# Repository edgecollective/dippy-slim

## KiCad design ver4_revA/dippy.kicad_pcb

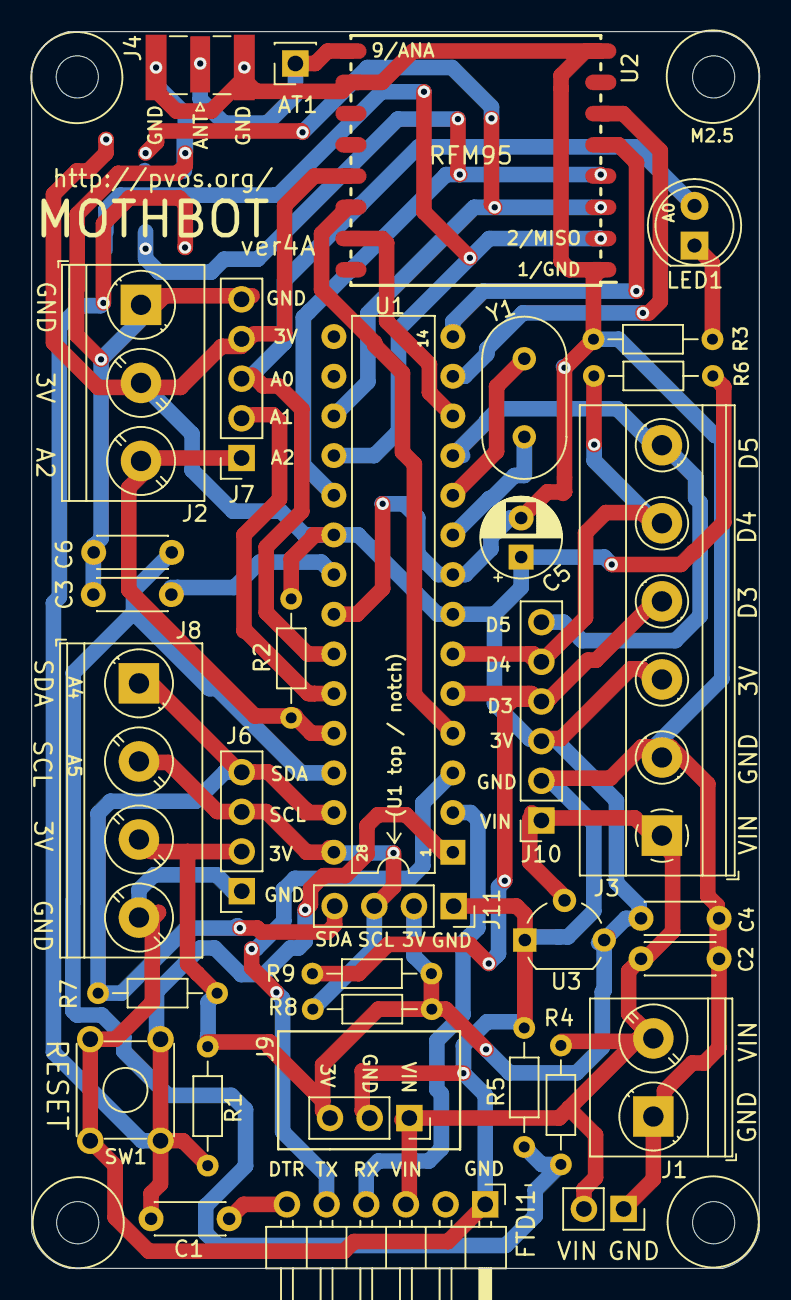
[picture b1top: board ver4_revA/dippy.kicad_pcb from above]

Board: 2 copper layers, 46.6 x 79.2 mm, 39 parts (1 on the bottom side), 28 nets.

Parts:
AT1: Conn_01x01_Female; PinSocket_1x01_P2.54mm_Vertical
C1, C2, C3, C4: 0.1u; C_Disc_D4.3mm_W1.9mm_P5.00mm
C5: 10u; CP_Radial_D5.0mm_P2.50mm
C6: 0.1uF; C_Disc_D4.3mm_W1.9mm_P5.00mm
FTDI1: Conn_01x06_Male; PinHeader_1x06_P2.54mm_Horizontal
H1, H2, H3, H4: MountingHole; MountingHole_2.7mm_M2.5
J1: Screw_Terminal_01x02; TerminalBlock_Phoenix_PT-1,5-2-5.0-H_1x02_P5.00mm_Horizontal
J2: Screw_Terminal_01x03; TerminalBlock_Phoenix_PT-1,5-3-5.0-H_1x03_P5.00mm_Horizontal
J3: Screw_Terminal_01x06; TerminalBlock_Phoenix_MKDS-1,5-6_1x06_P5.00mm_Horizontal
J4: Conn_Coaxial; SMA_Samtec_SMA-J-P-X-ST-EM1_EdgeMount
J5: Conn_02x03_Odd_Even; PinSocket_2x03_P2.54mm_Vertical_SMD
J6, J11: Conn_01x04_Female; PinSocket_1x04_P2.54mm_Vertical
J7: Conn_01x05_Female; PinSocket_1x05_P2.54mm_Vertical
J8: Screw_Terminal_01x04; TerminalBlock_Phoenix_PT-1,5-4-5.0-H_1x04_P5.00mm_Horizontal
J9: Conn_01x03_Female; PinSocket_1x03_P2.54mm_Vertical
J10: Conn_01x06_Female; PinSocket_1x06_P2.54mm_Vertical
J12: Conn_01x02_Female; PinSocket_1x02_P2.54mm_Vertical
LED1: LED; LED_D5.0mm
R1, R2, R3, R9: 10K; R_Axial_DIN0204_L3.6mm_D1.6mm_P7.62mm_Horizontal
R4, R5: 10M; R_Axial_DIN0204_L3.6mm_D1.6mm_P7.62mm_Horizontal
R6: 300R; R_Axial_DIN0204_L3.6mm_D1.6mm_P7.62mm_Horizontal
R7, R8: R; R_Axial_DIN0204_L3.6mm_D1.6mm_P7.62mm_Horizontal
SW1: SW_Push_Dual; SW_TH_Tactile_Omron_B3F-10xx
U1: ATmega328P-PU-C; DIP-28_W7.62mm
U2: RFM95W-915S2; RFM95
U3: MCP1700-3302E_TO92; TO-92_Wide
Y1: Crystal; Resonator-2Pin_W10.0mm_H5.0mm

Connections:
A0: J7.3, LED1.2, U1.23
A1: J7.2, U1.24
A2: J2.3, J7.1, R2.2, U1.25
A3: C6.1, R4.2, R5.1, U1.26
A4: J6.4, J8.1, J11.4, R7.2, U1.27
A5: J6.3, J8.2, J11.3, R8.2, U1.28
D2: U1.4, U2.14
D3: J3.4, J10.4, R9.2, U1.5
D4: J3.5, J10.5, R3.2, U1.6
D5: J3.6, J10.6, U1.11
D6: U1.12, U2.15
D7: U1.13, U2.6
D8: U1.14, U2.5
GND: C2.2, C3.2, C4.2, C5.2, C6.2, FTDI1.1, J1.1, J2.1, J3.2, J4.2, J5.6, J6.1, J7.5, J8.4, J9.2, J10.2, J11.1, J12.1, R5.2, R6.2, SW1.3, SW1.4, U1.8, U1.22, U2.1, U2.8, U2.10, U3.1
MISO: J5.1, U1.18, U2.2
MOSI: J5.4, U1.17, U2.3
unnamed: AT1.1, J4.1, U2.9
unnamed: C1.2, FTDI1.6
unnamed: C3.1, U1.21
unnamed: LED1.1, R6.1
unnamed: U1.9, Y1.1
unnamed: U1.10, Y1.2
RST: C1.1, J5.5, R1.2, SW1.1, SW1.2, U1.1
RX0: FTDI1.4, U1.2
SCK: J5.3, U1.19, U2.4
TX0: FTDI1.5, U1.3
VCC: C4.1, C5.1, J2.2, J3.3, J5.2, J6.2, J7.4, J8.3, J9.3, J10.3, J11.2, R1.1, R2.1, R3.1, R7.1, R8.1, R9.1, U1.7, U1.20, U2.13, U3.3
VIN: C2.1, FTDI1.3, J1.2, J3.1, J9.1, J10.1, J12.2, R4.1, U3.2

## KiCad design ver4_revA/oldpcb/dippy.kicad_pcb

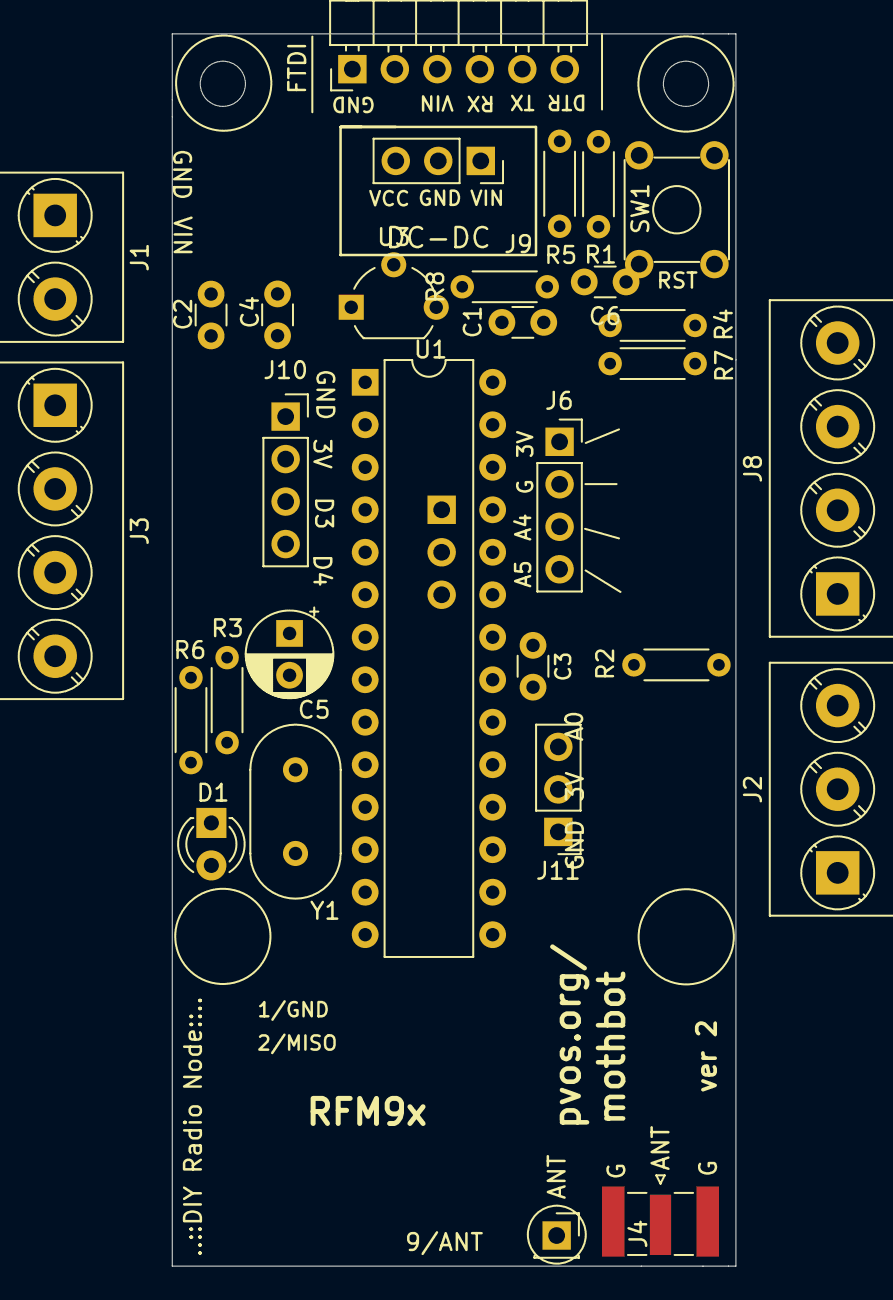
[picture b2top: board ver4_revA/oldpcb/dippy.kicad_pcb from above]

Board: 2 copper layers, 33.7 x 73.7 mm, 35 parts (1 on the bottom side), 21 nets, no tracks yet.

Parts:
AT1: Conn_01x01_Female; PinSocket_1x01_P2.54mm_Vertical
C1, C2, C3, C4: 0.1u; C_Disc_D3.0mm_W1.6mm_P2.50mm
C5: 10u; CP_Radial_D5.0mm_P2.50mm
C6: 0.1uF; C_Disc_D3.0mm_W1.6mm_P2.50mm
D1: LED; LED_D3.0mm
FTDI1: Conn_01x06_Male; PinHeader_1x06_P2.54mm_Horizontal
H1, H2, H3, H4: MountingHole; MountingHole_2.7mm_M2.5
J1: Screw_Terminal_01x02; TerminalBlock_Phoenix_PT-1,5-2-5.0-H_1x02_P5.00mm_Horizontal
J2: Screw_Terminal_01x03; TerminalBlock_Phoenix_PT-1,5-3-5.0-H_1x03_P5.00mm_Horizontal
J3, J8: Screw_Terminal_01x04; TerminalBlock_Phoenix_PT-1,5-4-5.0-H_1x04_P5.00mm_Horizontal
J4: Conn_Coaxial; SMA_Samtec_SMA-J-P-X-ST-EM1_EdgeMount
J6, J10: Conn_01x04_Female; PinSocket_1x04_P2.54mm_Vertical
J7, J11: Conn_01x03_Female; PinHeader_1x03_P2.54mm_Vertical
J9: Conn_01x03_Female; PinSocket_1x03_P2.54mm_Vertical
R1, R2, R3: 10K; R_Axial_DIN0204_L3.6mm_D1.6mm_P5.08mm_Horizontal
R4, R5: 10M; R_Axial_DIN0204_L3.6mm_D1.6mm_P5.08mm_Horizontal
R6: 300R; R_Axial_DIN0204_L3.6mm_D1.6mm_P5.08mm_Horizontal
R7, R8: R; R_Axial_DIN0204_L3.6mm_D1.6mm_P5.08mm_Horizontal
SW1: SW_Push_Dual; SW_TH_Tactile_Omron_B3F-10xx
U1: ATmega328P-PU-C; DIP-28_W7.62mm
U3: MCP1700-3302E_TO92; TO-92_Wide
Y1: Crystal; Resonator-2Pin_W10.0mm_H5.0mm

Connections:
A0: J2.3, J11.3, R2.2, U1.23
A1: J7.2, U1.24
A2: J7.1, U1.25
A3: C6.1, R4.2, R5.1, U1.26
A4: J6.4, J8.1, R7.2, U1.27
A5: J6.3, J8.2, R8.2, U1.28
D3: J3.3, J10.3, U1.5
D4: J3.4, J10.4, R3.2, U1.6
D5: D1.2, U1.11
GND: C2.2, C3.2, C4.2, C5.2, C6.2, FTDI1.1, J1.1, J2.1, J3.1, J4.2, J6.2, J7.3, J8.3, J9.2, J10.1, J11.1, R5.2, R6.2, SW1.3, SW1.4, U1.8, U1.22, U3.1
unnamed: AT1.1, J4.1
unnamed: C1.2, FTDI1.6
unnamed: C3.1, U1.21
unnamed: D1.1, R6.1
unnamed: U1.9, Y1.1
unnamed: U1.10, Y1.2
RST: C1.1, R1.2, SW1.1, SW1.2, U1.1
RX0: FTDI1.4, U1.2
TX0: FTDI1.5, U1.3
VCC: C4.1, C5.1, J2.2, J3.2, J6.1, J8.4, J9.3, J10.2, J11.2, R1.1, R2.1, R3.1, R7.1, R8.1, U1.7, U1.20, U3.3
VIN: C2.1, FTDI1.3, J1.2, J9.1, R4.1, U3.2
